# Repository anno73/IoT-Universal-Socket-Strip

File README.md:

# This is work in progress ...

# IoT Universal Socket Strip

Ever wanted to have a customizable socket strip? Now you can... 
This project enhances an [Ehmann](https://www.ehmann-gmbh.de/en/) [Universal Socket Strip](https://www.ehmann-gmbh.de/en/produkte/steckdosensysteme/steckdosenleisten/) 
like the [8-fold strip 0200x00082301](https://www.ehmann-gmbh.de/wp-content/uploads/2017/01/0200x00082301_0200x00082303_0200x00082305-data-sheet.pdf)
with custom relay controller and dedicated switching PCBs for each of the sockets.

The controller PCB is ESP8266 based, ideal for integration into your home IoT installation via e.g. MQTT.

# ToDo

Write firmware

Design power/controller and relay board.

Hardware, Software, Controller PCB, Relay PCB, Supporting Documents

# Best Practice Tutorials

## Git
[Using .gitignore the Right Way](https://labs.consol.de/development/git/2017/02/22/gitignore.html)

https://www.xspdf.com/resolution/57309756.html

## KiCad
[Better manage KiCAD projects using Git](https://medium.com/inventhub/better-manage-kicad-projects-using-git-8d06e1310af8)

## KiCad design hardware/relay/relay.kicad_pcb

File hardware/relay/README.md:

# Relay Module PCB

One module for each socket.

# Next board revision

As of (AN2519)[http://ww1.microchip.com/downloads/en/Appnotes/AN2519-AVR-Microcontroller-Hardware-Design-Considerations-00002519B.pdf]

Add pull up resistor to RESET-Vcc (>10k)

Add cap between RESET-GND (100nF) - only if not using DebugWIRE

? Add diode between RESET-Vcc

V Add resistor between RESET-External_RESET_header

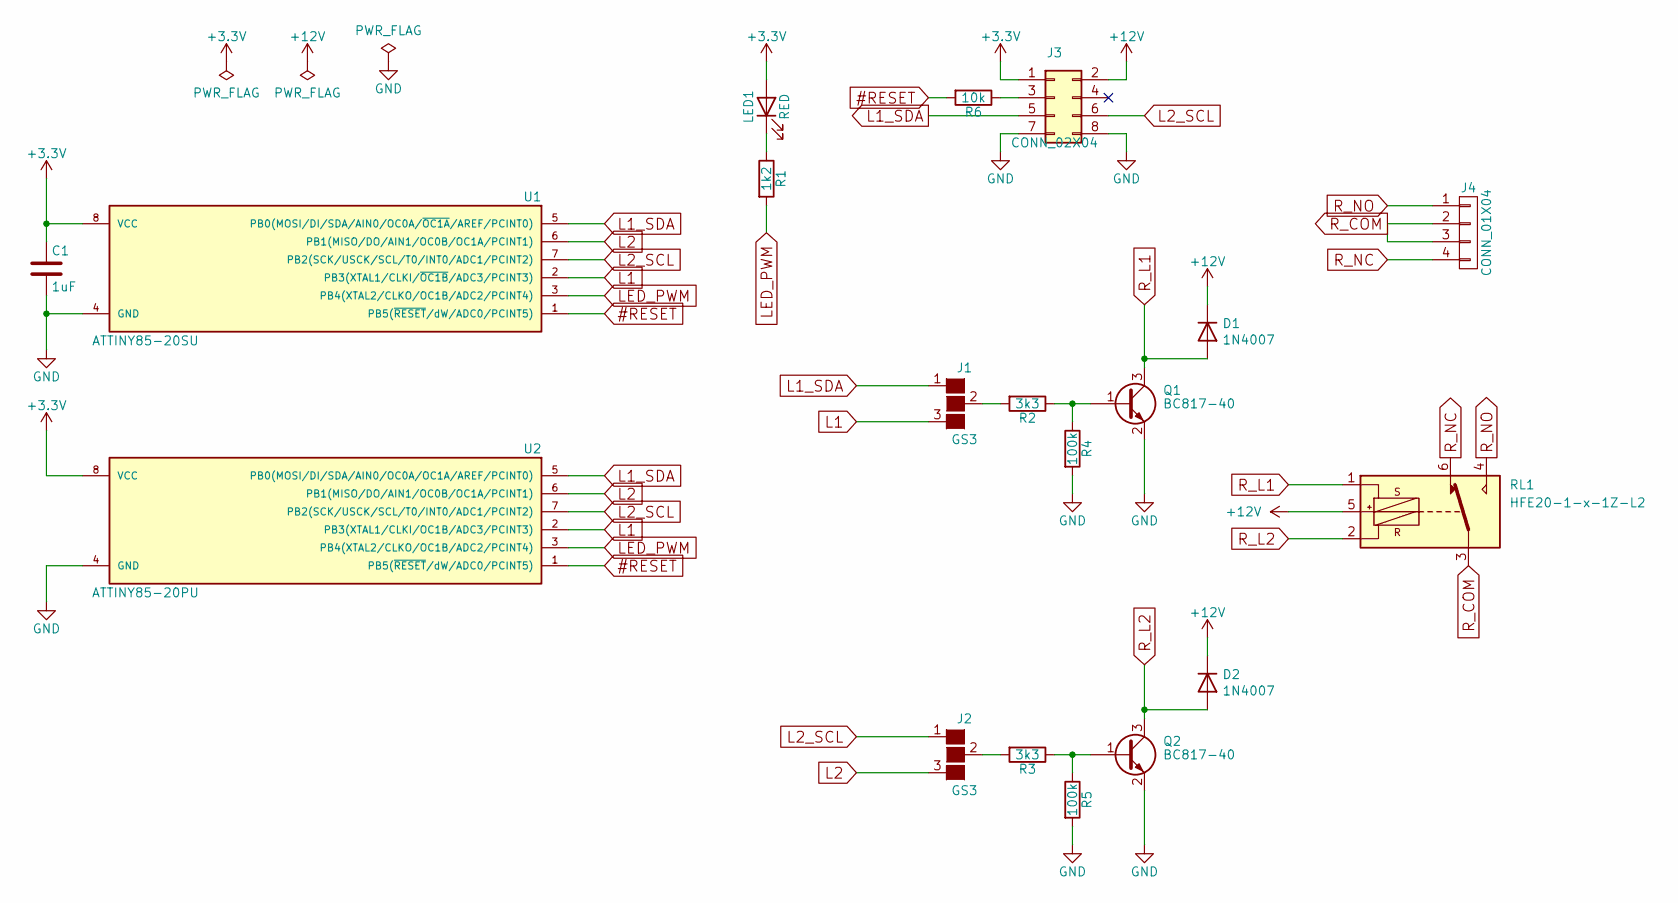
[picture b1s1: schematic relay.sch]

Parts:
C1: 1uF; C_0805_HandSoldering
D1, D2: 1N4007; D_SMA_Handsoldering
J1, J2: GS3
J3: CONN_02X04; Pin_Header_Straight_2x04_Pitch2.54mm
J4: CONN_01X04; SR21504VBNC
LED1: RED; LED_0805_HandSoldering
Q1, Q2: BC817-40; SOT-23_Handsoldering
R1: 1k2; R_0805_HandSoldering
R2, R3: 3k3; R_0805_HandSoldering
R4, R5: 100k; R_0805_HandSoldering
R6: 10k; R_0805_HandSoldering
RL1: HFE20-1-x-1Z-L2; HFE20-1_DPST_Double_Coil_Bistable
U1: ATTINY85-20SU; SOIC-8_3.9x4.9mm_Pitch1.27mm
U2: ATTINY85-20PU; DIP-8_W7.62mm_Socket

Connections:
#RESET: R6.2, U1.1 (PB5(~RESET~/dW/ADC0/PCINT5)), U2.1 (PB5(~RESET~/dW/ADC0/PCINT5))
+3V3: C1.1, J3.1, LED1.2 (A), U1.8 (VCC), U2.8 (VCC)
+12V: D1.1 (K), D2.1 (K), J3.2, RL1.5
GND: C1.2, J3.7, J3.8, Q1.2 (E), Q2.2 (E), R4.2, R5.2, U1.4 (GND), U2.4 (GND)
L1: J1.3 (G3), U1.2 (PB3(XTAL1/CLKI/~OC1B~/ADC3/PCINT3)), U2.2 (PB3(XTAL1/CLKI/OC1B/ADC3/PCINT3))
L1_SDA: J1.1 (G1), J3.5, U1.5 (PB0(MOSI/DI/SDA/AIN0/OC0A/~OC1A~/AREF/P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), U2.5 (PB0(MOSI/DI/SDA/AIN0/OC0A/OC1A/AREF/PCI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)
L2: J2.3 (G3), U1.6 (PB1(MISO/DO/AIN1/OC0B/OC1A/PCINT1)), U2.6 (PB1(MISO/DO/AIN1/OC0B/OC1A/PCINT1))
L2_SCL: J2.1 (G1), J3.6, U1.7 (PB2(SCK/USCK/SCL/T0/INT0/ADC1/PCINT2)), U2.7 (PB2(SCK/USCK/SCL/T0/INT0/ADC1/PCINT2))
LED_PWM: R1.2, U1.3 (PB4(XTAL2/CLKO/OC1B/ADC2/PCINT4)), U2.3 (PB4(XTAL2/CLKO/OC1B/ADC2/PCINT4))
unnamed: J1.2 (G2), R2.2
unnamed: J2.2 (G2), R3.2
unnamed: J3.3, R6.1
unnamed: LED1.1 (K), R1.1
unnamed: Q1.1 (B), R2.1, R4.1
unnamed: Q2.1 (B), R3.1, R5.1
R_COM: J4.2, J4.3, RL1.3
R_L1: D1.2 (A), Q1.3 (C), RL1.1
R_L2: D2.2 (A), Q2.3 (C), RL1.2
R_NC: J4.4, RL1.6
R_NO: J4.1, RL1.4

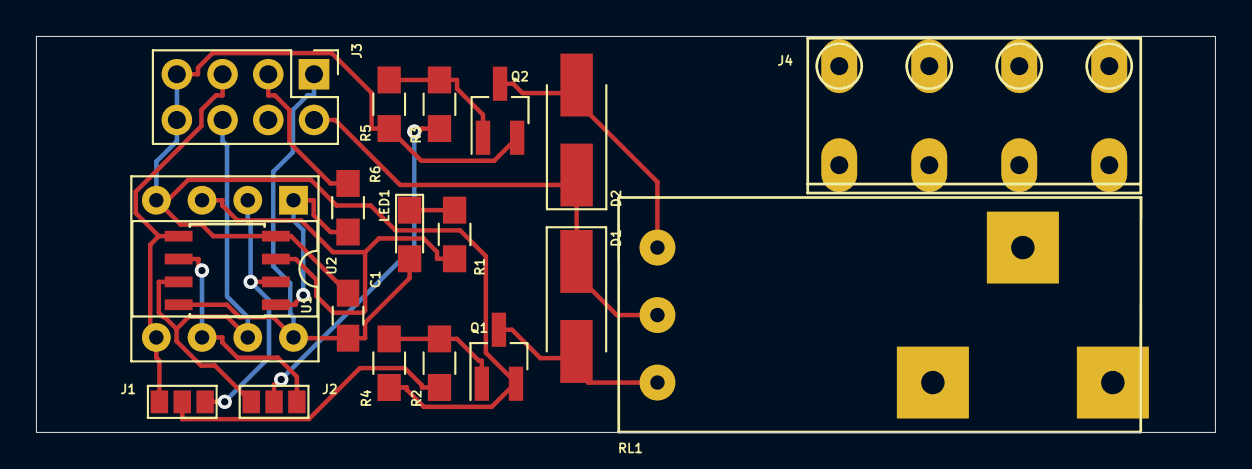
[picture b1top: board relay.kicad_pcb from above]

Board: 2 copper layers, 65.5 x 22.0 mm, 19 parts (0 on the bottom side), 20 nets.

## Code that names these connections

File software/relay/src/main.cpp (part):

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 * 
 * ATTiny   Port  Arduino   Function
 * Pin #    Pin   Pin # 
 *   1      PB5    5/A0     /RESET
 *   2      PB3    3/A3
 *   3      PB4    4/A2
 *   4      -       -       GND
 *   5      PB0     0       IIC SDA
 *   6      PB1     1
 *   7      PB2    2/A1     IIC SCL
 *   8              -       VCC
 */

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
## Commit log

2021-01-13 Initial
2021-01-13 various
2021-01-15 Initial version of controller
2021-01-19 Fix relay footprint
2021-01-19 Introduce enum for iic commands
2021-01-19 Introduce some more enum
2021-01-19 sparkfun digiSpark DEV board
2021-01-20 Debugging, documentation
2021-01-20 add reset logic
2021-01-20 words
2021-01-20 switch to nodemcu, add IOTWC debug
2021-01-20 add mqttHeartbeat configuration to IOTWC
2021-01-20 test delay() vs millis() hack vs PolledTimeout
2021-01-20 renamed
2021-01-20 tab spacing, comments
2021-01-20 Add mqtt commands for relay and led
2021-01-20 add docu
2021-01-28 Set digispark as dev board
2021-01-28 cspell
2021-01-28 digispark
2021-01-28 docu
2021-01-28 refactor, fix request of non existing iic register
2021-01-29 Extend commandset
2021-01-29 extend commands
2021-01-29 refactor
2021-01-30 clenaup
2021-01-30 cleanup
2021-01-30 Save config to EEPROM and EEPROM Wear Level
2021-01-31 change package to tiny/tinyx5
2021-01-31 Add debugging with SendOnlySoftwareSerial
2021-01-31 Watchdog timer, docu, typos
2021-01-31 Alwasy show IP not only when debugging enabled.
2021-01-31 Enable IOTWC debugging
2021-01-31 mqtt: Introduce ../get/.. commands
2021-01-31 Search for new modules and initialize
2021-01-31 comment
2021-01-31 Fix typos
2021-01-31 map mqtt relay index to iic address
2021-02-01 New hidden iic register, split debug log to use cases
2021-02-01 Give gerbers for PCB fab a less generic name
2021-02-01 Add power flag, convert label to global labels, add R to protect #RESET
2021-02-01 whatever
2021-02-01 Fix relay footprint, swap relay and 240V terminals, rearange logic components for easier part placement.
2021-02-06 Switch to DigistumpArduino for dev board
2021-02-07 Debugging, REGSPECIAL, fix IIC register select
2021-02-07 typo
2021-02-07 Read from relay module, fix read timeout
2021-02-10 Correct path and url
2021-02-13 upgarde digistumpcore to 1.7.1
2021-02-13 add vi .swp
2021-02-13 Initial version
2021-02-13 docu ESP8266 Wire.setClockStretchLimit
2021-02-20 add file
2021-02-20 Add command buffer to process in loop
2021-02-20 reorder statusReg update
2021-02-20 docu - status busy flag
2021-02-20 New Debug target, register bit consts, busy flag handling
